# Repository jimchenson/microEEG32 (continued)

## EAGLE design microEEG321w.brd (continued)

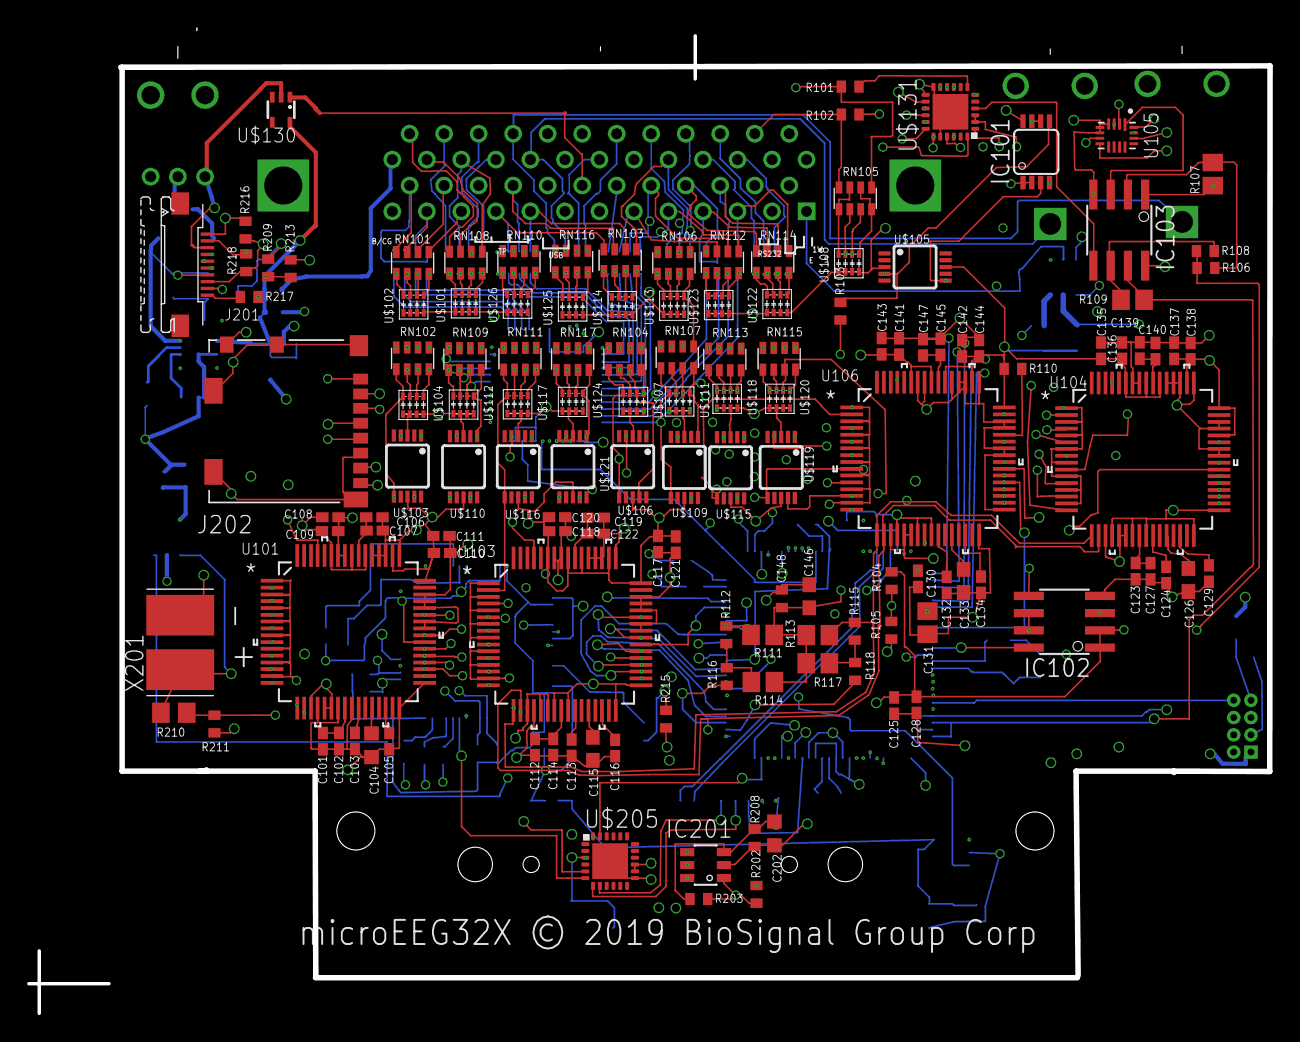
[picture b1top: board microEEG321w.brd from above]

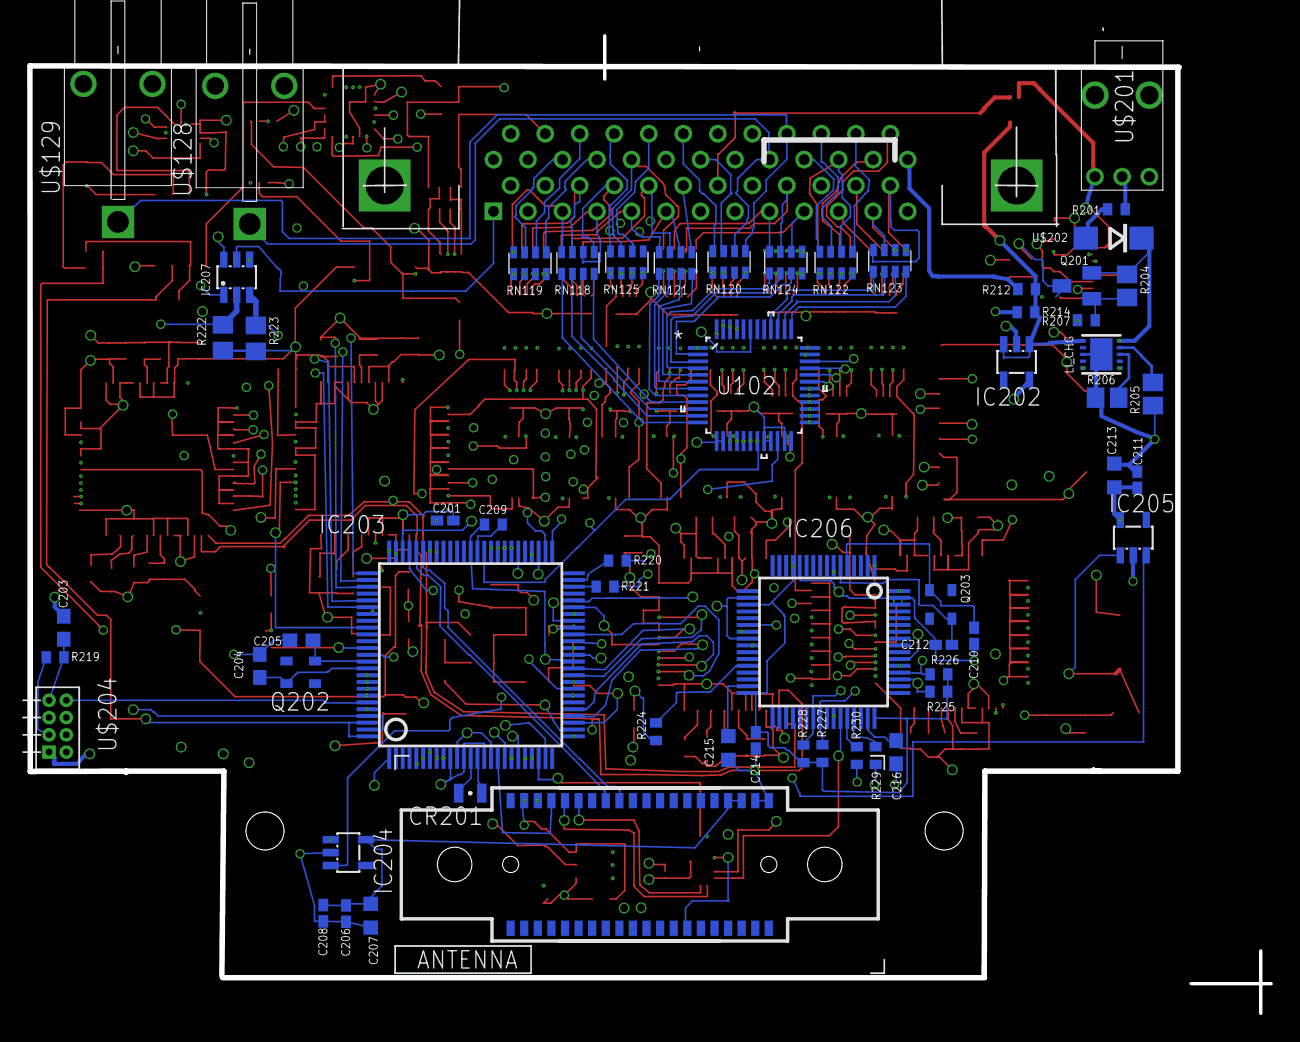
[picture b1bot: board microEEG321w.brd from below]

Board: 10 copper layers, 91.3 x 72.5 mm, 197 parts (61 on the bottom side), 289 nets.
